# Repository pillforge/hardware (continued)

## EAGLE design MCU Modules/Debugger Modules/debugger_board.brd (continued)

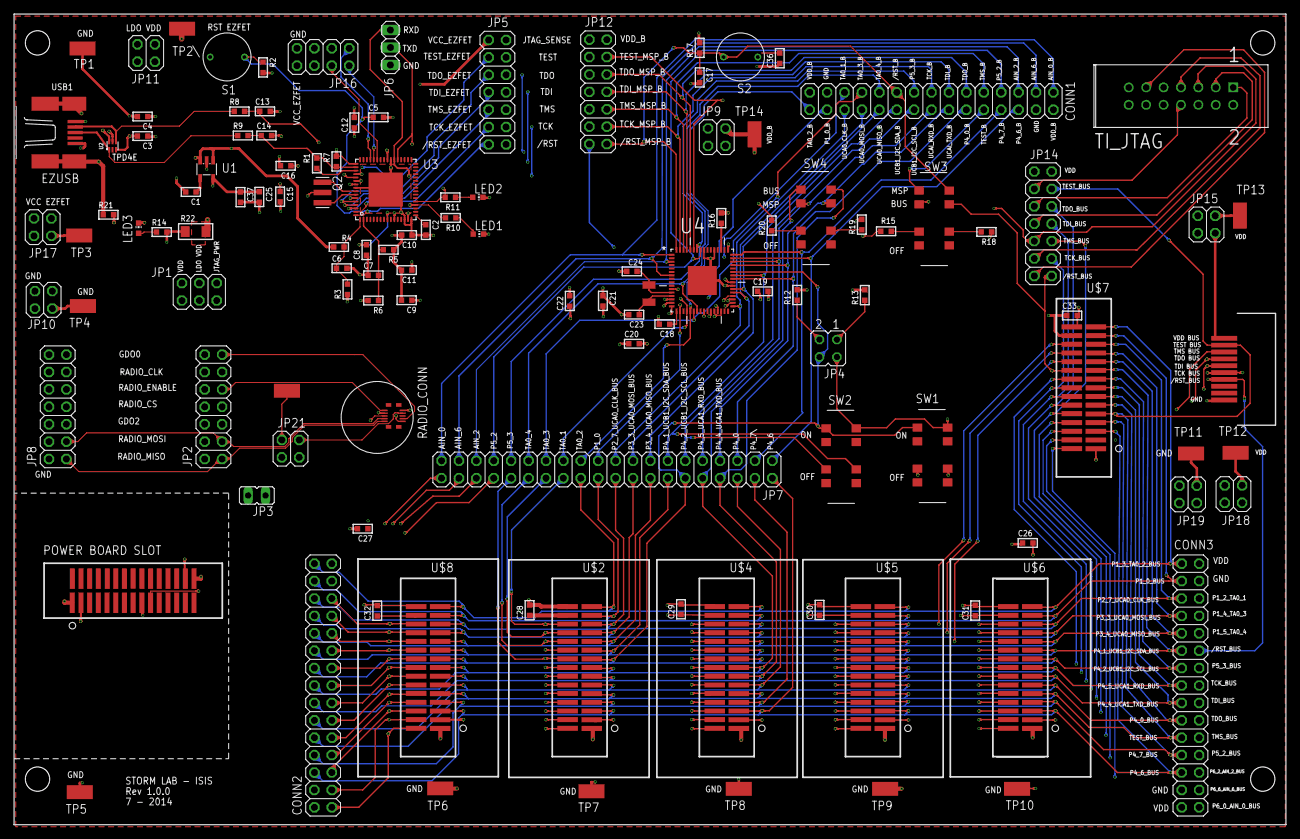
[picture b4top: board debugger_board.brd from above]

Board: 4 copper layers, 185.6 x 118.3 mm, 120 parts (0 on the bottom side), 125 nets.

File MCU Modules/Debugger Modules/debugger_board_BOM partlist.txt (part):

Part       Value                              Device                       Package					SUPPLIER				SUPPLIER PART NUMBER	
				                  
C1         10n                                C_0603                       C0603                    DIGI-KEY                490-1512-1-ND                                                                      
C2         470n                               C_0603                       C0603                    DIGI-KEY                490-1539-1-ND                                      
C3         100n                               C_0603                       C0603                    DIGI-KEY                311-1343-1-ND                    
C4         10u                                C_0603                       C0603                    DIGI-KEY                587-3383-1-ND                      
C5         1n                                 C_0603                       C0603                    DIGI-KEY                490-1494-1-ND                       
C6         33p                                C_0603                       C0603                    DIGI-KEY                399-1055-1-ND                               
C7         33p                                C_0603                       C0603                    DIGI-KEY                399-1055-1-ND                                
C8         100n                               C_0603                       C0603                    DIGI-KEY                311-1343-1-ND                              
C9         100n                               C_0603                       C0603                    DIGI-KEY                311-1343-1-ND                                    
C10        100n                               C_0603                       C0603                    DIGI-KEY                311-1343-1-ND                                    
C11        10u                                C_0603                       C0603          	    DIGI-KEY                587-3383-1-ND                                                                 
C12        100n                               C_0603                       C0603                    DIGI-KEY                311-1343-1-ND                                                                             
C13        10p                                C_0603                       C0603                    DIGI-KEY                712-1308-1-ND                                                               
C14        10p                                C_0603                       C0603                    DIGI-KEY                712-1308-1-ND                                                               
C15        220n                               C_0603                       C0603                    DIGI-KEY                445-1318-1-ND                                                             
C16        220n                               C_0603                       C0603                    DIGI-KEY                445-1318-1-ND                                                              
C17        10n                                C_0603                       C0603                    DIGI-KEY                490-1512-1-ND                                                             
C18        470n                               C_0603                       C0603                    DIGI-KEY                490-1539-1-ND                                                             
C19        100n                               C_0603                       C0603                    DIGI-KEY                311-1343-1-ND                                                                             
C20        100n                               C_0603                       C0603                    DIGI-KEY                311-1343-1-ND                                                                             
C21        100n                               C_0603                       C0603                    DIGI-KEY                311-1343-1-ND                                                                             
C22        10u                                C_0603                       C0603                    DIGI-KEY                587-3383-1-ND                                                             
C23        12p                                C_0603                       C0603		    DIGI-KEY		    1276-1254-1-ND										                                                                                                 
C24        12p                                C_0603                       C0603                    DIGI-KEY		    1276-1254-1-ND	                                                                             
C25        10u                                C_0603                       C0603                    DIGI-KEY                587-3383-1-ND                                                     
C26        100n                               C_0603                       C0603                    DIGI-KEY                311-1343-1-ND                                                                             
C27        100n                               C_0603                       C0603                    DIGI-KEY                311-1343-1-ND                                                                             
C28        100n                               C_0603                       C0603                    DIGI-KEY                311-1343-1-ND                                                                             
C29        100n                               C_0603                       C0603                    DIGI-KEY                311-1343-1-ND                                                                             
C30        100n                               C_0603                       C0603                    DIGI-KEY                311-1343-1-ND                                                                             
C31        100n                               C_0603                       C0603                    DIGI-KEY                311-1343-1-ND                                                                             
C32        100n                               C_0603                       C0603                    DIGI-KEY                311-1343-1-ND                                                                             
C33        100n                               C_0603                       C0603                    DIGI-KEY                311-1343-1-ND                                                                             
C36        100n                               C_0603                       C0603                    DIGI-KEY                311-1343-1-ND                                                                             
C37        100n                               C_0603                       C0603                    DIGI-KEY                311-1343-1-ND                                                                             
CONN1      HEADER MSP430_B                    PINHD-2X15                   2X15                     DIGI-KEY                609-3456-ND                                                      
CONN2      HEADER BUS A                       PINHD-2X15                   2X15                     DIGI-KEY                609-3456-ND                                                    
CONN3      HEADER BUS B                       PINHD-2X15                   2X15                     DIGI-KEY                609-3456-ND                                                    
EZUSB      USB!                               MINI-USB-SHIELD	           UX60A-MB-5ST             DIGI-KEY                H2961CT-ND                                                     
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
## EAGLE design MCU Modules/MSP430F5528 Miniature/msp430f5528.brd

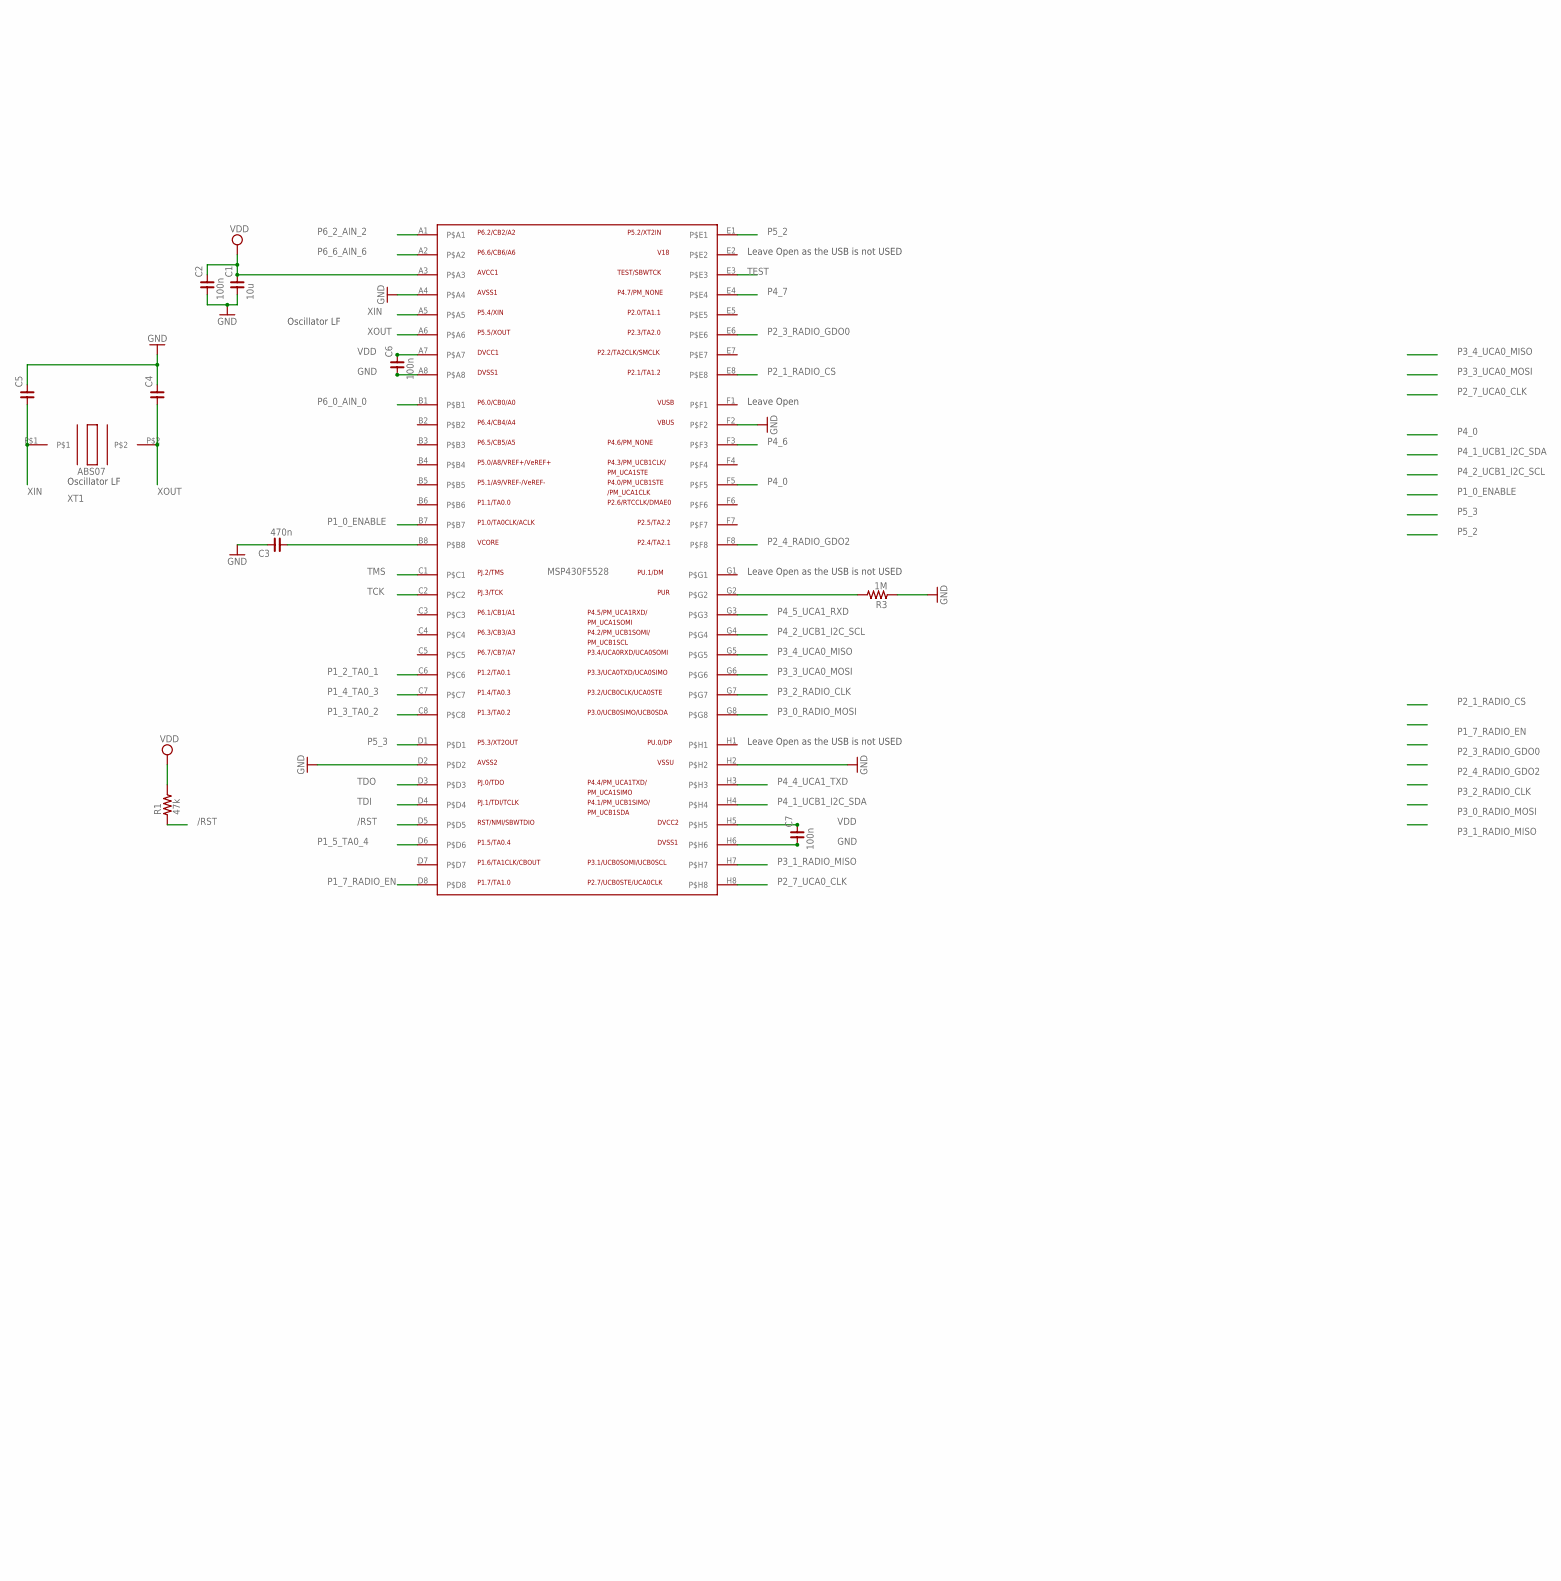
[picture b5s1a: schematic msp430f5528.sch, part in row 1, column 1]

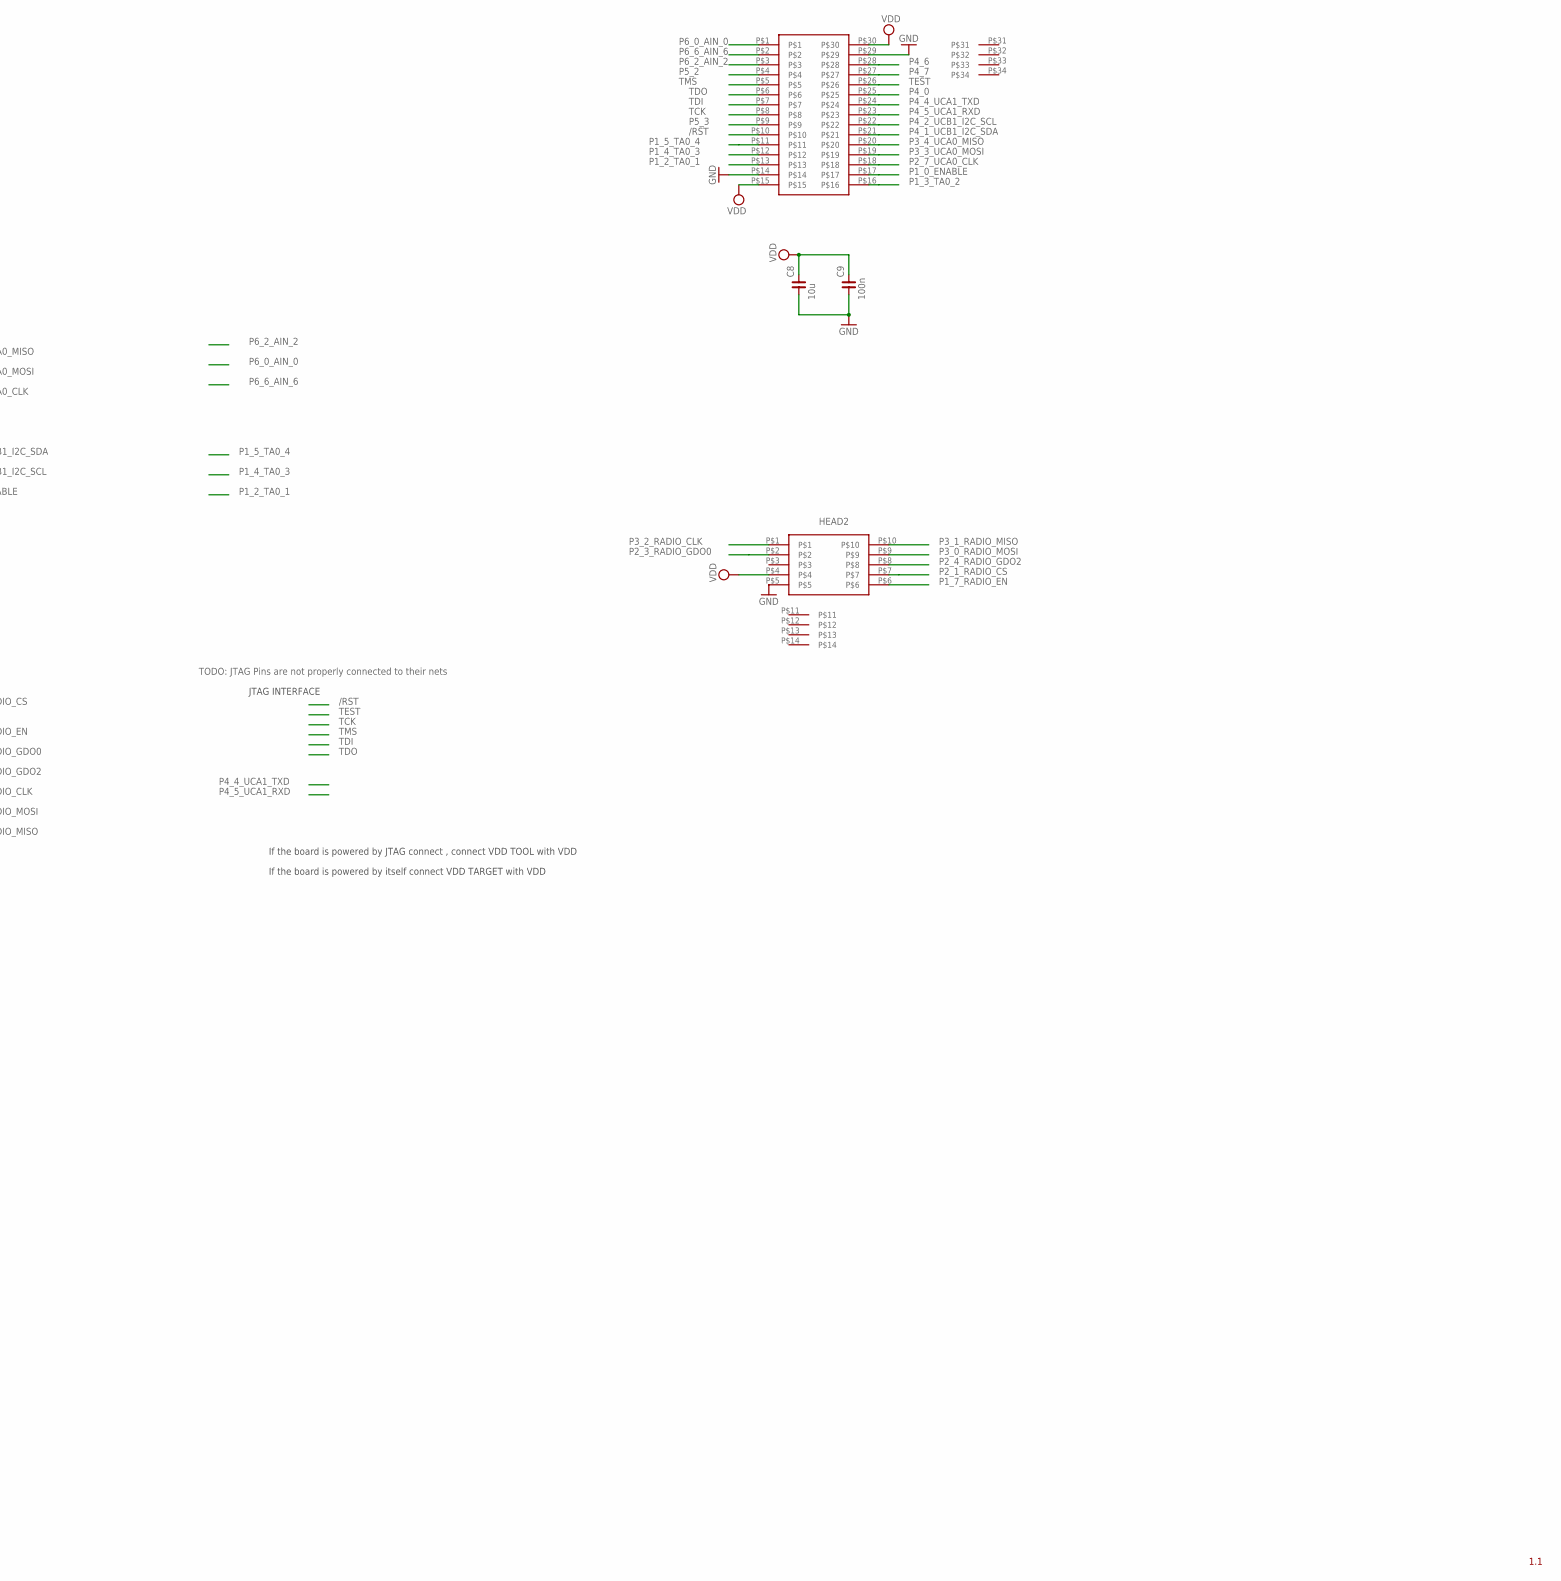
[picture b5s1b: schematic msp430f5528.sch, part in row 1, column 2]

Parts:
C1, C8: 10u; C0402
C2, C6, C7, C9: 100n; C0402
C3: 470n; C0402
C4, C5: C_0402; C0402
R1: 47k; R0402
R3: 1M; R0402
U$1: MSP430F5528; YFF64
U$2: OSC32K; ABS07
U$4: 55909-0374_PLUG
U$5: 559099872_2X5_PLUG

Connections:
/RST: R1.1, U$1.D5, U$4.P$10
GND: C1.1, C2.1, C3.2, C4.2, C5.2, C6.1, C7.1, C8.1, C9.1, R3.1, U$1.A4, U$1.A8, U$1.D2, U$1.F2, U$1.H2, U$1.H6, U$4.P$14, U$4.P$29, U$5.P$5
unnamed: C3.1, U$1.B8
unnamed: R3.2, U$1.G2
P1_0_ENABLE: U$1.B7, U$4.P$17
P1_2_TA0_1: U$1.C6, U$4.P$13
P1_3_TA0_2: U$1.C8, U$4.P$16
P1_4_TA0_3: U$1.C7, U$4.P$12
P1_5_TA0_4: U$1.D6, U$4.P$11
P1_7_RADIO_EN: U$1.D8, U$5.P$6
P2_1_RADIO_CS: U$1.E8, U$5.P$7
P2_3_RADIO_GDO0: U$1.E6, U$5.P$2
P2_4_RADIO_GDO2: U$1.F8, U$5.P$8
P2_7_UCA0_CLK: U$1.H8, U$4.P$18
P3_0_RADIO_MOSI: U$1.G8, U$5.P$9
P3_1_RADIO_MISO: U$1.H7, U$5.P$10
P3_2_RADIO_CLK: U$1.G7, U$5.P$1
P3_3_UCA0_MOSI: U$1.G6, U$4.P$19
P3_4_UCA0_MISO: U$1.G5, U$4.P$20
P4_0: U$1.F5, U$4.P$25
P4_1_UCB1_I2C_SDA: U$1.H4, U$4.P$21
P4_2_UCB1_I2C_SCL: U$1.G4, U$4.P$22
P4_4_UCA1_TXD: U$1.H3, U$4.P$24
P4_5_UCA1_RXD: U$1.G3, U$4.P$23
P4_6: U$1.F3, U$4.P$28
P4_7: U$1.E4, U$4.P$27
P5_2: U$1.E1, U$4.P$4
P5_3: U$1.D1, U$4.P$9
P6_0_AIN_0: U$1.B1, U$4.P$1
P6_2_AIN_2: U$1.A1, U$4.P$3
P6_6_AIN_6: U$1.A2, U$4.P$2
TCK: U$1.C2, U$4.P$8
TDI: U$1.D4, U$4.P$7
TDO: U$1.D3, U$4.P$6
TEST: U$1.E3, U$4.P$26
TMS: U$1.C1, U$4.P$5
VDD: C1.2, C2.2, C6.2, C7.2, C8.2, C9.2, R1.2, U$1.A3, U$1.A7, U$1.H5, U$4.P$15, U$4.P$30, U$5.P$4
XIN: C5.1, U$1.A5, U$2.P$1
XOUT: C4.1, U$1.A6, U$2.P$2

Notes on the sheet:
Oscillator LF
Leave Open as the USB is not USED
Leave Open
XT1
If the board is powered by JTAG connect , connect VDD TOOL with VDD
If the board is powered by itself connect VDD TARGET with VDD
JTAG INTERFACE
TODO: JTAG Pins are not properly connected to their nets
HEAD2
1.1

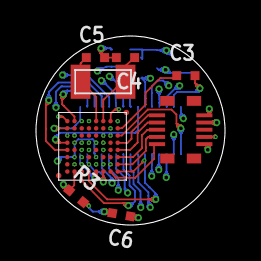
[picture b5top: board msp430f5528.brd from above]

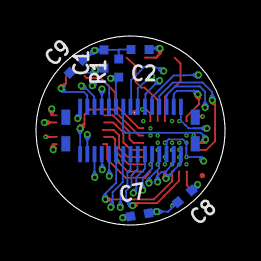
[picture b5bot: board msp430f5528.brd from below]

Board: 6 copper layers, 10.5 x 10.5 mm, 15 parts (7 on the bottom side), 39 nets.
